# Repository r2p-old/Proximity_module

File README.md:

Proximity_module
================

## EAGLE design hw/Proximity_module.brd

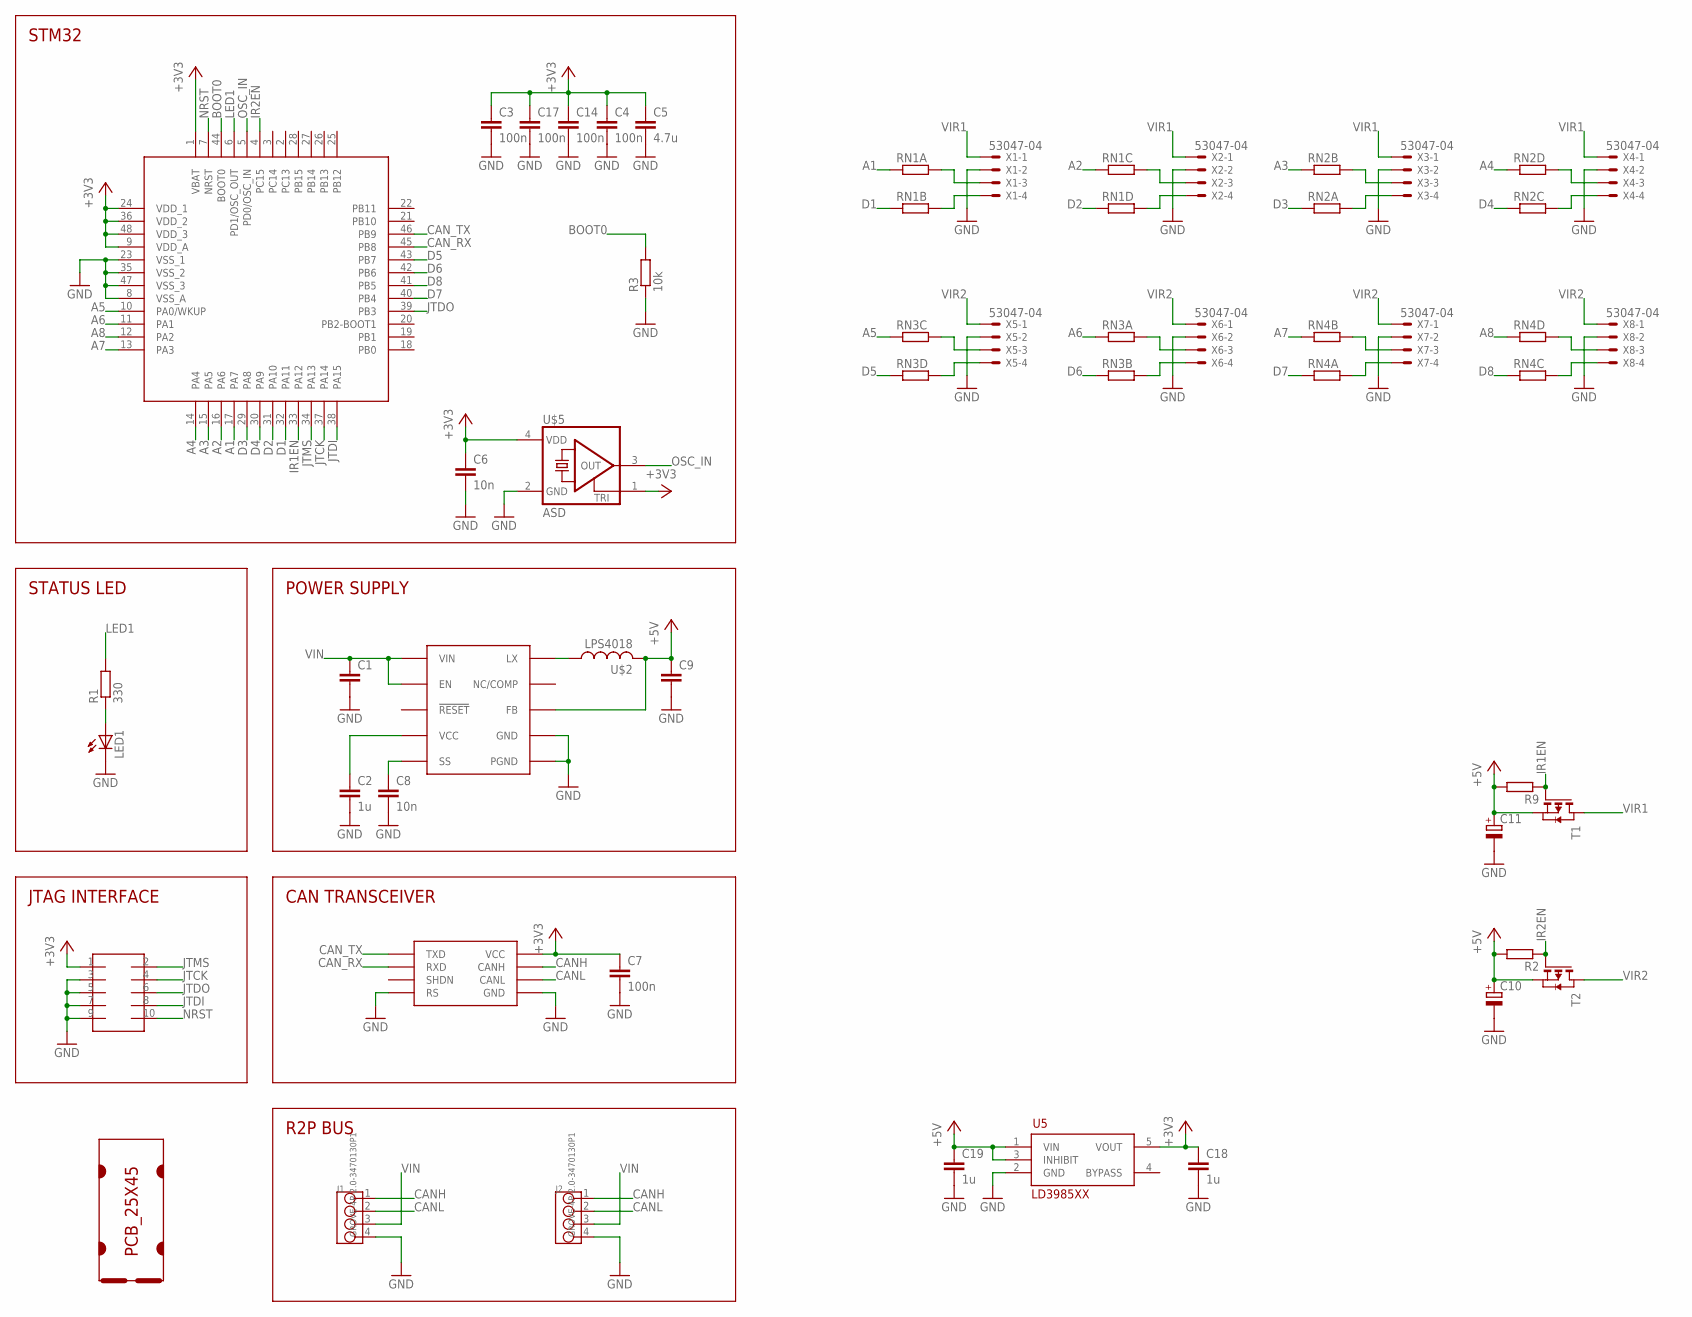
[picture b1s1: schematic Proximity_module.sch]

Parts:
C1: C-EUC1206; C1206
C2, C18, C19: 1u; C0603
C3, C4, C7, C14, C17: 100n; C0603
C5: 4.7u; C0805
C6, C8: 10n; C0603
C9: C-EUC0805; C0805
C10, C11: CPOL-EUB/3528-21R; B/3528-21R
J1, J2: GROVE-4P-2.0-3470130P1; 4P-2.0
LED1: LEDCHIPLED_0805; CHIPLED_0805
R1: 330; R0603
R2, R9: R-EU_R0603; R0603
R3: 10k; R0603
RN1, RN2, RN3, RN4: RESISTOR_ARRAY_4; RN8P-4R-CRA06S
SOT1: MAX3051EKA; SOT23-8L
T1, T2: PMOSSOT23; SOT-23
U5: LD3985XX; SOT23-5L
U$1: PCB_25X45; 25X45
U$2: LPS4018
U$3: MAX17501; TDFN-10
U$4: FTSH-105TH; FTSH-105-TH
U$5: ASD; 2.5X2
U$6: STM32F103CXTX; LQFP48
X1, X2, X3, X4, X5, X6, X7, X8: 53047-04

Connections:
+3V3: C3.1, C4.1, C5.1, C6.1, C7.1, C14.1, C17.1, C18.1, SOT1.3 (VCC), U5.5 (VOUT), U$4.1, U$5.1 (TRI), U$5.4 (VDD), U$6.1 (VBAT), U$6.9 (VDD_A), U$6.24 (VDD_1), U$6.36 (VDD_2), U$6.48 (VDD_3)
+5V: C9.1, C10.+, C11.+, C19.1, R2.2, R9.2, T1.2 (S), T2.2 (S), U5.1 (VIN), U5.3 (INHIBIT), U$2.P$2 (2), U$3.P$5 (FB)
A1: RN1.1, U$6.17 (PA7)
A2: RN1.3 (1), U$6.16 (PA6)
A3: RN2.2 (1), U$6.15 (PA5)
A4: RN2.4 (1), U$6.14 (PA4)
A5: RN3.3 (1), U$6.10 (PA0/WKUP)
A6: RN3.1, U$6.11 (PA1)
A7: RN4.2 (1), U$6.13 (PA3)
A8: RN4.4 (1), U$6.12 (PA2)
BOOT0: R3.2, U$6.44 (BOOT0)
CANH: J1.1, J2.1, SOT1.7 (CANH)
CANL: J1.2, J2.2, SOT1.6 (CANL)
CAN_RX: SOT1.4 (RXD), U$6.45 (PB8)
CAN_TX: SOT1.1 (TXD), U$6.46 (PB9)
D1: RN1.2 (1), U$6.32 (PA11)
D2: RN1.4 (1), U$6.31 (PA10)
D3: RN2.1, U$6.29 (PA8)
D4: RN2.3 (1), U$6.30 (PA9)
D5: RN3.4 (1), U$6.43 (PB7)
D6: RN3.2 (1), U$6.42 (PB6)
D7: RN4.1, U$6.40 (PB4)
D8: RN4.3 (1), U$6.41 (PB5)
GND: C1.2, C2.2, C3.2, C4.2, C5.2, C6.2, C7.2, C8.2, C9.2, C10.-, C11.-, C14.2, C17.2, C18.2, C19.2, J1.4, J2.4, LED1.C, R3.1, SOT1.2 (GND), SOT1.8 (RS), U5.2 (GND), U$3.P$1 (PGND), U$3.P$9 (GND), U$3.P$11 (PGND), U$4.3, U$4.5, U$4.7, U$4.9, U$5.2 (GND), U$6.8 (VSS_A), U$6.23 (VSS_1), U$6.35 (VSS_2), U$6.47 (VSS_3), X1.2, X2.2, X3.2, X4.2, X5.2, X6.2, X7.2, X8.2
IR1EN: R9.1, T1.3 (G), U$6.33 (PA12)
IR2EN: R2.1, T2.3 (G), U$6.4 (PC15)
JTCK: U$4.4, U$6.37 (PA14)
JTDI: U$4.8, U$6.38 (PA15)
JTDO: U$4.6, U$6.39 (PB3)
JTMS: U$4.2, U$6.34 (PA13)
LED1: R1.2, U$6.6 (PD1/OSC_OUT)
unnamed: U$2.P$1 (1), U$3.P$10 (LX)
unnamed: RN1.8 (2), X1.3
unnamed: LED1.A, R1.1
unnamed: RN1.7 (2), X1.4
unnamed: C2.1, U$3.P$4 (VCC)
unnamed: C8.1, U$3.P$6 (SS)
unnamed: RN1.6 (2), X2.3
unnamed: RN1.5 (2), X2.4
unnamed: RN2.7 (2), X3.3
unnamed: RN2.8 (2), X3.4
unnamed: RN2.5 (2), X4.3
unnamed: RN2.6 (2), X4.4
unnamed: RN4.5 (2), X8.3
unnamed: RN4.6 (2), X8.4
unnamed: RN4.7 (2), X7.3
unnamed: RN4.8 (2), X7.4
unnamed: RN3.8 (2), X6.3
unnamed: RN3.7 (2), X6.4
unnamed: RN3.6 (2), X5.3
unnamed: RN3.5 (2), X5.4
NRST: U$4.10, U$6.7 (NRST)
OSC_IN: U$5.3 (OUT), U$6.5 (PD0/OSC_IN)
VIN: C1.1, J1.3, J2.3, U$3.P$2 (VIN), U$3.P$3 (EN)
VIR1: T1.1 (D), X1.1, X2.1, X3.1, X4.1
VIR2: T2.1 (D), X5.1, X6.1, X7.1, X8.1

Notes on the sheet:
STM32
STATUS LED
JTAG INTERFACE
POWER SUPPLY
CAN TRANSCEIVER
R2P BUS

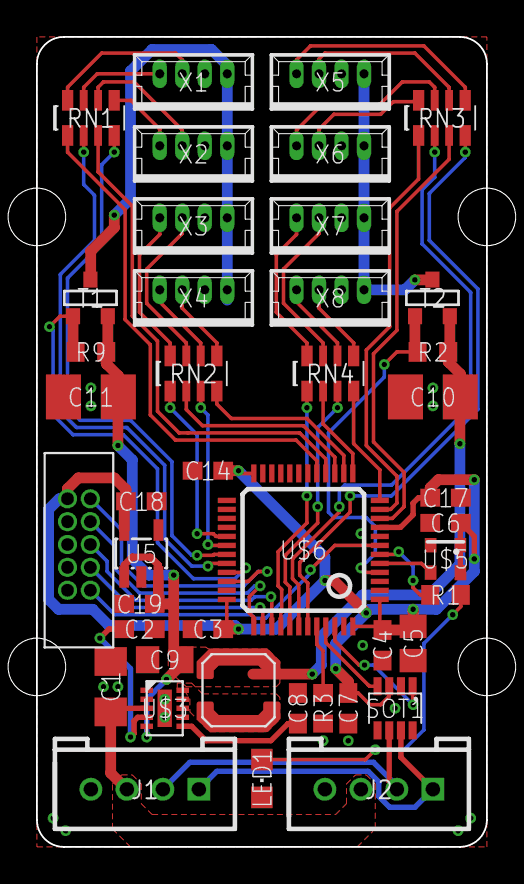
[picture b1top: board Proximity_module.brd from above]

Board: 2 copper layers, 25.0 x 45.0 mm, 44 parts (0 on the bottom side), 56 nets.

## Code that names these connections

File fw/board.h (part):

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/*
 * GPIOA setup:
 *
 * PA0  - PIN0                      (input pullup).
 * PA1  - PIN1                      (input pullup).
 * PA2  - PIN2                      (input pullup).
 * PA3  - PIN3                      (input pullup).
 * PA4  - PIN4                      (input pullup).
 * PA5  - PIN5                      (input pullup).
 * PA6  - PIN6                      (input pullup).
 * PA7  - PIN7                      (input pullup).
 * PA8  - PIN8                      (input pullup).
 * PA9  - PIN9                      (input pullup).
 * PA10 - PIN10                     (input pullup).
 * PA11 - PIN11                     (input pullup).
 * PA12 - PIN12                     (input pullup).
 * PA13 - JTAG_TMS                  (alternate 0).
 * PA14 - JTAG_TCK                  (alternate 0).
 * PA15 - JTAG_TDI                  (alternate 0).
 */
#define VAL_GPIOA_MODER             (PIN_MODE_INPUT(GPIOA_PIN0) |           \
                                     PIN_MODE_INPUT(GPIOA_PIN1) |           \
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 * PB0  - PIN0                      (input pullup).
 * PB1  - PIN1                      (input pullup).
 * PB2  - PIN2                      (input pullup).
 * PB3  - JTAG_TDO                  (alternate 0).
 * PB4  - JTAG_TRST                 (alternate 0).
 * PB5  - PIN5                      (input pullup).
 * PB6  - PIN6                      (input pullup).
 * PB7  - PIN7                      (input pullup).
 * PB8  - CAN_RX                    (alternate 9).
 * PB9  - CAN_TX                    (alternate 9).
 * PB10 - PIN10                     (input pullup).
 * PB11 - PIN11                     (input pullup).
 * PB12 - PIN12                     (input pullup).
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 * PC12 - PIN12                     (input pullup).
 * PC13 - PIN13                     (input pullup).
 * PC14 - OSC32_IN                  (input floating).
 * PC15 - PIN15                     (input pullup).
 */
#define VAL_GPIOC_MODER             (PIN_MODE_INPUT(GPIOC_PIN0) |           \
                                     PIN_MODE_INPUT(GPIOC_PIN1) |           \
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/*
 * GPIOD setup:
 *
 * PD0  - PIN0                      (input pullup).
 * PD1  - PIN1                      (input pullup).
 * PD2  - PIN2                      (input pullup).
 * PD3  - PIN3                      (input pullup).
 * PD4  - PIN4                      (input pullup).
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/*
 * GPIOF setup:
 *
 * PF0  - OSC_IN                    (input floating).
 * PF1  - LED                       (output pushpull maximum).
 * PF2  - PIN2                      (input pullup).
 * PF3  - PIN3                      (input pullup).
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
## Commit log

2014-06-05 layout completed
2014-06-23 Added makefile for quicker gerber generation
2014-06-24 added PNG of board layout
2014-07-31 added blinking led firmware
2014-12-16 small fixes for production
2014-12-29 approved DRC false errors
2015-01-08 added logo to bottom silkscreen
2015-01-13 minor fixes for manufacturing
2015-01-22 added assembly PDF generation

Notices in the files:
fw/board.h:
ChibiOS/RT - Copyright (C) 2006-2013 Giovanni Di Sirio
Licensed under the Apache License, Version 2.0 (the "License");
